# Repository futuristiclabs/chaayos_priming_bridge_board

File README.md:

# Chaayos Priming Bridge Board

Bridge board project (Atopile / `.ato`) for reading 4x non-contact liquid level sensors and exporting status over I2C to a host MCU.

## Project Goal

- Use four non-contact liquid level sensors mounted on process lines:
  - `WATER_1`
  - `WATER_2`
  - `MILK_1`
  - `MILK_2`
- Perform local signal conditioning / interface conversion on this bridge board.
- Send priming status for all four lines to the host machine over I2C.

## Sensor Interface (Per Channel)

Expected sensor-side wiring:

- `VCC`
- `GND`
- `SIG` (digital state)
- `MODE` / toggle line (if used for behavior inversion)

## Bridge Board Host Interface

Target host-side connector:

- `SCL`
- `SDA`
- `VCC`
- `GND`

Functional requirement: host side must implement a complete I2C bus (`SCL + SDA`) for status transfer.

## Priming Status Contract

Bridge board shall publish one digital priming status per channel:

- `WATER_1_PRIMED`
- `WATER_2_PRIMED`
- `MILK_1_PRIMED`
- `MILK_2_PRIMED`

Recommended host payload is a single status byte:

- bit0: `WATER_1_PRIMED`
- bit1: `WATER_2_PRIMED`
- bit2: `MILK_1_PRIMED`
- bit3: `MILK_2_PRIMED`
- bit4..bit7: reserved

## Implemented Schematic (Current)

Implemented in `main.ato` with the following architecture:

- I2C GPIO expander: `Texas Instruments TCA9534PWR` (`C783615`)
- Host connector: `JST B4B-XH-A` (4-pin)
- Sensor connectors: 4x `JST B4B-XH-A` (one per pipe)
- I2C pull-ups: 2x `4.7k` (0603)
- Decoupling capacitor: `100nF` (0603)

Host connector pin map:

- `P1 -> GND`
- `P2 -> SCL`
- `P3 -> SDA`
- `P4 -> VCC`

Sensor connector pin map (all 4 channels):

- `P1 -> VCC`
- `P2 -> GND`
- `P3 -> SIG`
- `P4 -> MODE` (currently tied to `GND`)

GPIO channel mapping:

- `P0 <- WATER_1 SIG`
- `P1 <- WATER_2 SIG`
- `P2 <- MILK_1 SIG`
- `P3 <- MILK_2 SIG`

I2C expander address straps:

- `A0 = GND`
- `A1 = GND`
- `A2 = GND`

## Local Sensor Schematic Assets

Saved in this repository:

- `docs/PRO RANGE-Y27C-Dx-NPN.pdf` (primary local datasheet, 10 pages)
- `docs/sensors/xkc_y25_connection_schematic.png` (sensor connection diagram)
- `docs/sensors/xkc_y25_pinout_board.png` (pinout/interface board reference)

Source reference page used:

- https://wiki.dfrobot.com/Non_Contact_Capacitive_Liquid_Level_Sensor_SKU_SEN0368

## Repo Structure (current)

- `main.ato` - top-level Atopile module entry
- `ato.yaml` - Atopile project/build config
- `layouts/` - PCB layout assets
- `docs/sensors/` - external sensor reference files

Created by Goutham Gandhi Nadendla <gouthamgandhi@ftlabs.io>

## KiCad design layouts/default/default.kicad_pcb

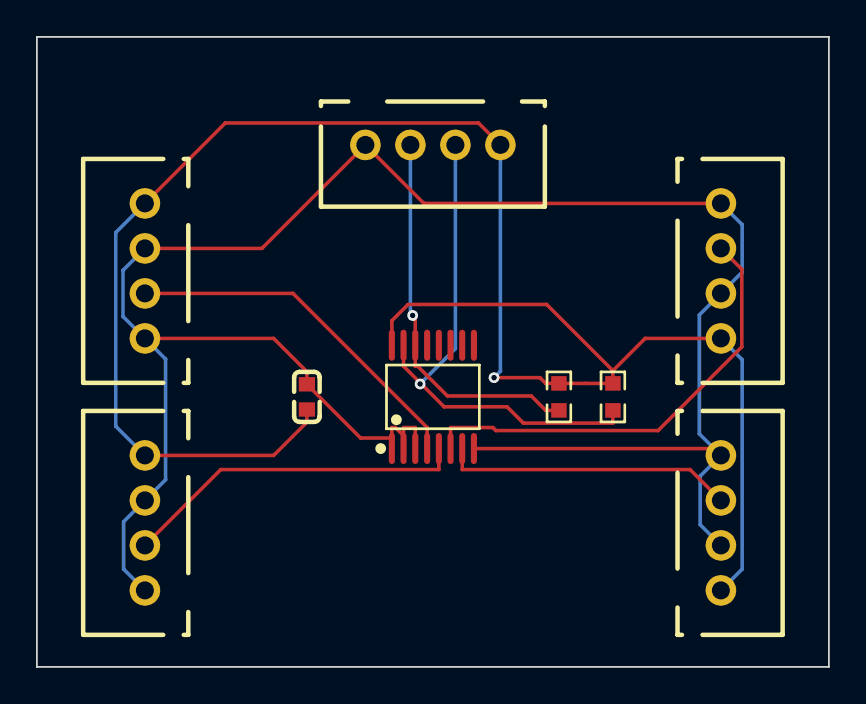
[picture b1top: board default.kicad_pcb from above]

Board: 2 copper layers, 44.0 x 35.0 mm, 9 parts (0 on the bottom side), 8 nets.

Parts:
C1: 0F; C0603
J1, J2, J3, J4, J5: CONN-TH_B4B-XH-A-LF-SN
R1, R2: 4700Ω; R0603
U1: TSSOP-16_L5.0-W4.4-P0.65-LS6.4-BL

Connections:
3: J4.3, U1.4
3-1: J5.3, U1.5
3-2: J2.3, U1.6
3-3: J3.3, U1.7
SCL: J1.2, R1.1, U1.14
SDA: J1.3, R2.1, U1.15
hv: C1.1, J1.4, J2.1, J3.1, J4.1, J5.1, R1.2, R2.2, U1.16
lv: C1.2, J1.1, J2.2, J2.4, J3.2, J3.4, J4.2, J4.4, J5.2, J5.4, U1.1, U1.2, U1.3, U1.8

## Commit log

2026-02-27 Implement compact H-layout board, routing/DRC cleanup, mounting holes, labels, and 3D model alignment fixes
